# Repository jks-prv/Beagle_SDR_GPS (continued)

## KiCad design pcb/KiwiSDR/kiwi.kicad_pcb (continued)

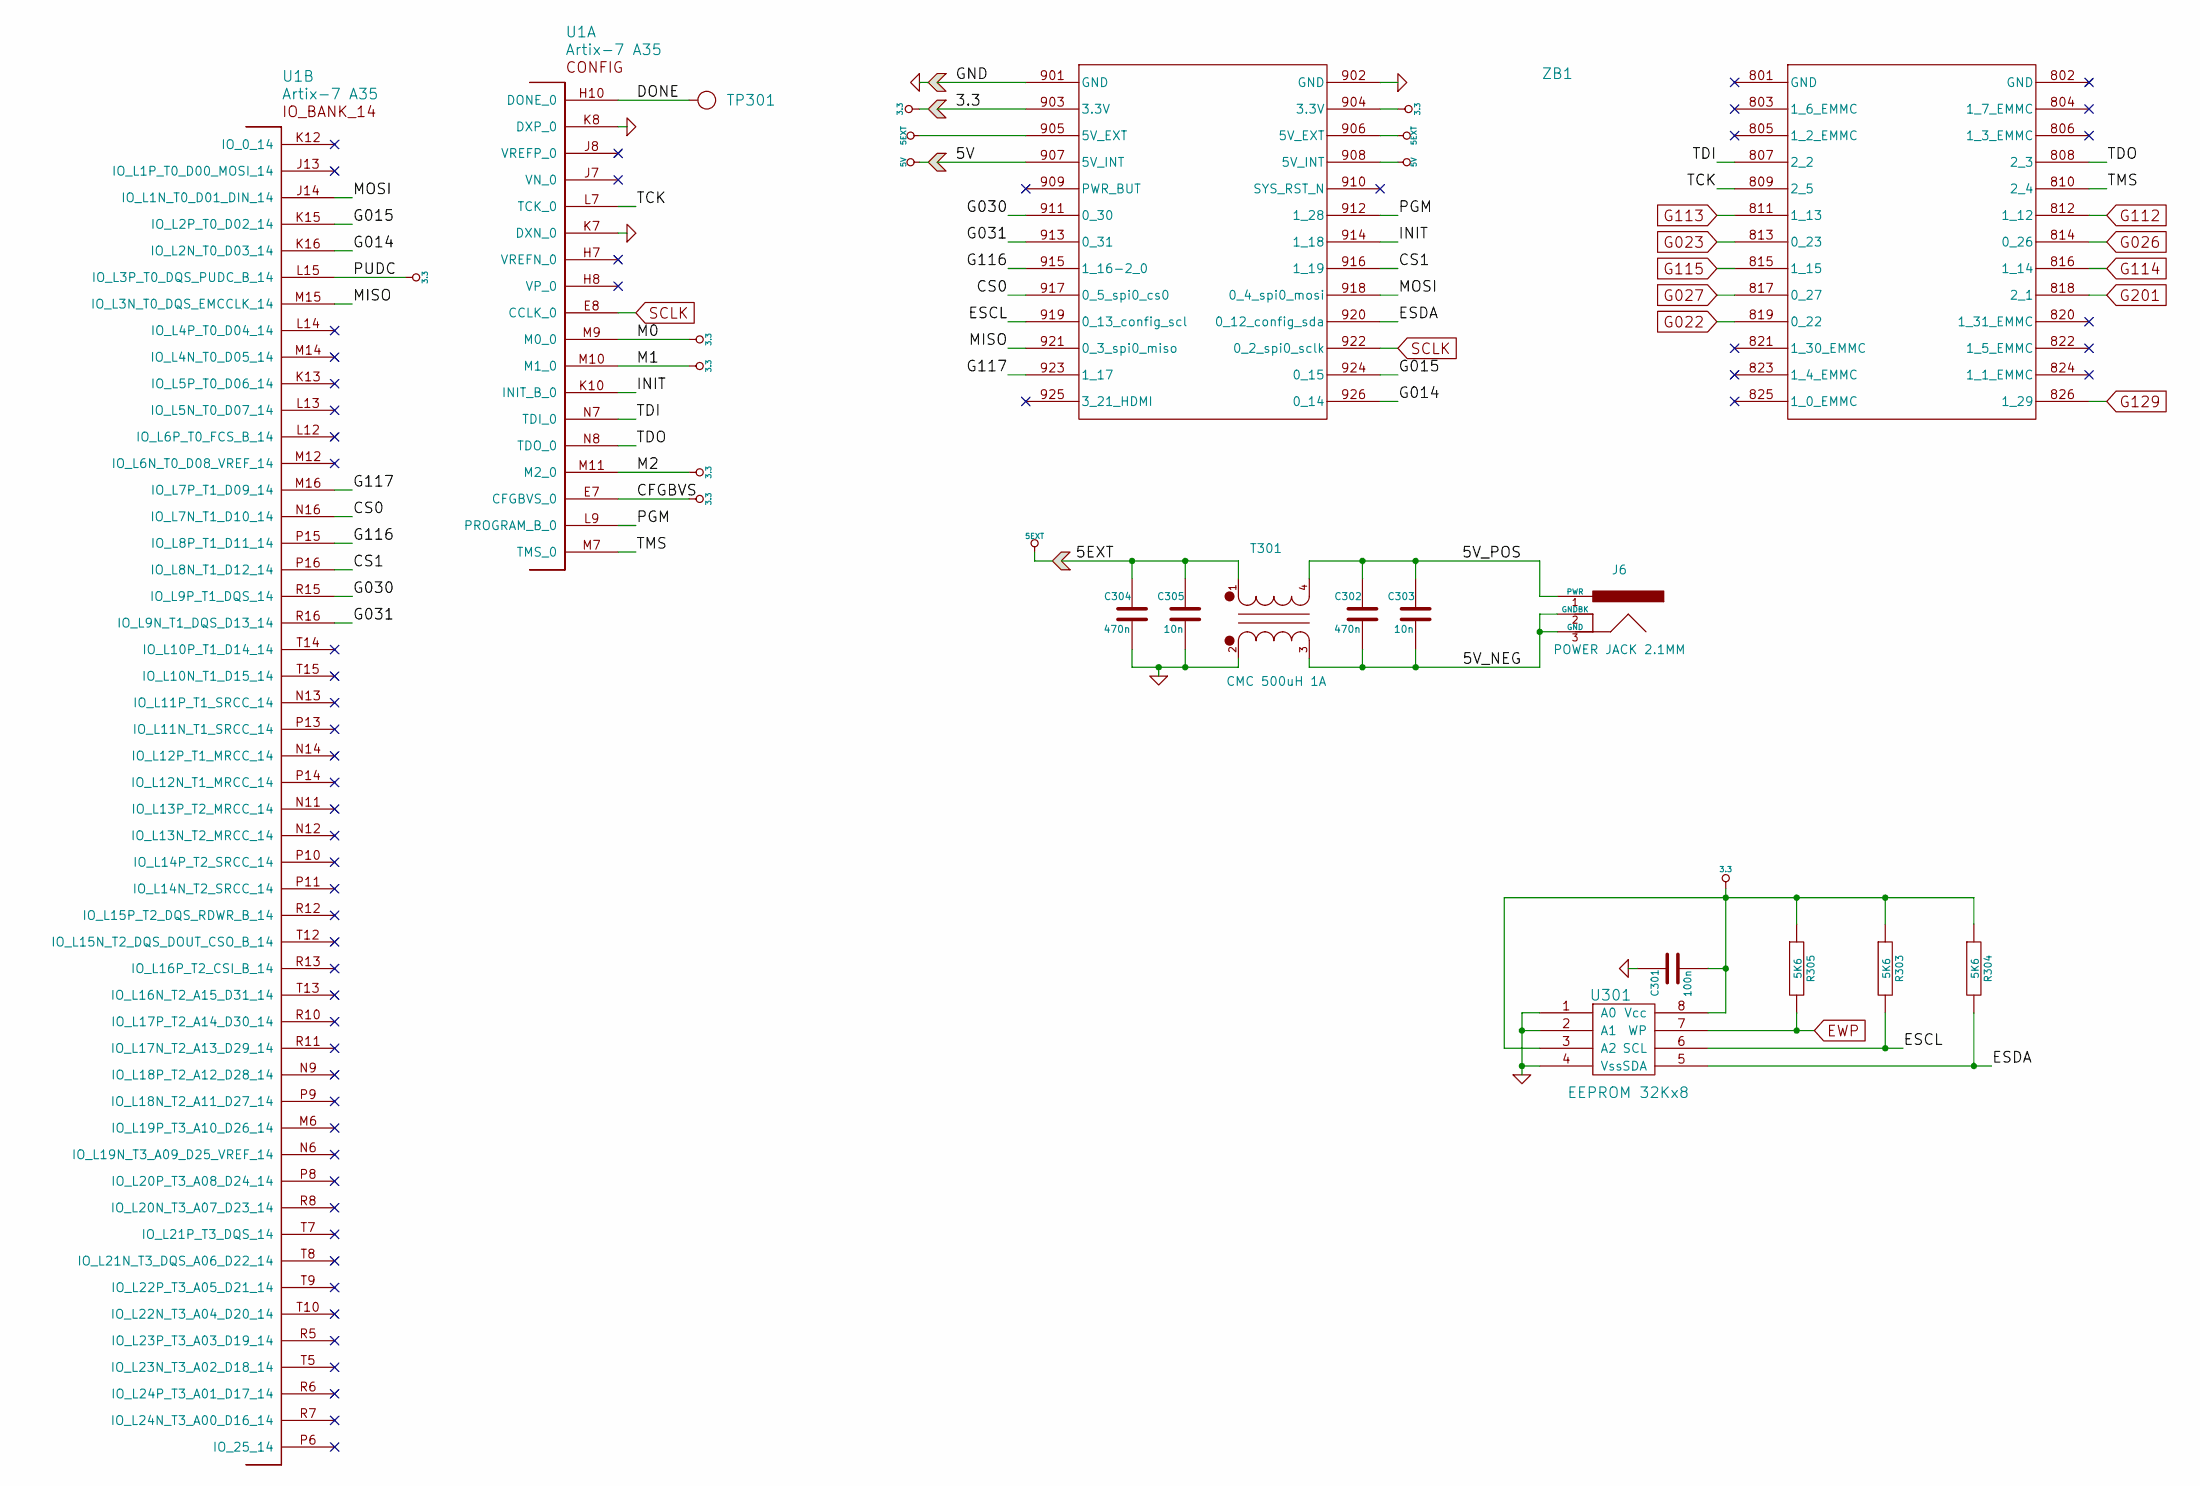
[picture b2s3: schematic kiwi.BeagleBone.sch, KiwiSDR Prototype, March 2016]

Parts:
C301: 100n; kiwi-SM0402
C302, C304: 470n; kiwi-SM0402
C303, C305: 10n; kiwi-SM0402
J6: POWER JACK 2.1MM; kiwi-JACK_2_1MM_TH
R303, R304, R305: 5K6; kiwi-SM0402
T301: CMC 500uH 1A; kiwi-CMC
TP301: TEST_POINT; kiwi-TP_VIA_600
U1: Artix-7 A35; kiwi-FTG256
U301: EEPROM 32Kx8; kiwi-TSSOP8
ZB1: HEADER 13x2; kiwi-BEAGLEBONE_BLACK

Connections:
/BeagleBone/5V_NEG: C302.2, C303.2, J6.2 (GNDBK), J6.3 (GND), T301.3
/BeagleBone/5V_POS: C302.1, C303.1, J6.1 (PWR), T301.4
/BeagleBone/CS0: U1.N16 (IO_L7N_T1_D10_14), ZB1.917 (0_5_spi0_cs0)
/BeagleBone/CS1: U1.P16 (IO_L8N_T1_D12_14), ZB1.916 (1_19)
/BeagleBone/DONE: TP301.1, U1.H10 (DONE_0)
/BeagleBone/ESCL: R303.2, U301.6 (SCL), ZB1.919 (0_13_config_scl)
/BeagleBone/ESDA: R304.2, U301.5 (SDA), ZB1.920 (0_12_config_sda)
/BeagleBone/G014: U1.K16 (IO_L2N_T0_D03_14), ZB1.926 (0_14)
/BeagleBone/G015: U1.K15 (IO_L2P_T0_D02_14), ZB1.924 (0_15)
/BeagleBone/G030: U1.R15 (IO_L9P_T1_DQS_14), ZB1.911 (0_30)
/BeagleBone/G031: U1.R16 (IO_L9N_T1_DQS_D13_14), ZB1.913 (0_31)
/BeagleBone/G116: U1.P15 (IO_L8P_T1_D11_14), ZB1.915 (1_16-2_0)
/BeagleBone/G117: U1.M16 (IO_L7P_T1_D09_14), ZB1.923 (1_17)
/BeagleBone/INIT: U1.K10 (INIT_B_0), ZB1.914 (1_18)
/BeagleBone/MISO: U1.M15 (IO_L3N_T0_DQS_EMCCLK_14), ZB1.921 (0_3_spi0_miso)
/BeagleBone/MOSI: U1.J14 (IO_L1N_T0_D01_DIN_14), ZB1.918 (0_4_spi0_mosi)
/BeagleBone/PGM: U1.L9 (PROGRAM_B_0), ZB1.912 (1_28)
/BeagleBone/TCK: U1.L7 (TCK_0), ZB1.809 (2_5)
/BeagleBone/TDI: U1.N7 (TDI_0), ZB1.807 (2_2)
/BeagleBone/TDO: U1.N8 (TDO_0), ZB1.808 (2_3)
/BeagleBone/TMS: U1.M7 (TMS_0), ZB1.810 (2_4)
EWP: R305.2, U301.7 (WP); also elsewhere on the board
G022: ZB1.819 (0_22); also elsewhere on the board
G023: ZB1.813 (0_23); also elsewhere on the board
G026: ZB1.814 (0_26); also elsewhere on the board
G027: ZB1.817 (0_27); also elsewhere on the board
G112: ZB1.812 (1_12); also elsewhere on the board
G113: ZB1.811 (1_13); also elsewhere on the board
G114: ZB1.816 (1_14); also elsewhere on the board
G115: ZB1.815 (1_15); also elsewhere on the board
G129: ZB1.826 (1_29); also elsewhere on the board
G201: ZB1.818 (2_1); also elsewhere on the board
SCLK: U1.E8 (CCLK_0), ZB1.922 (0_2_spi0_sclk); also elsewhere on the board

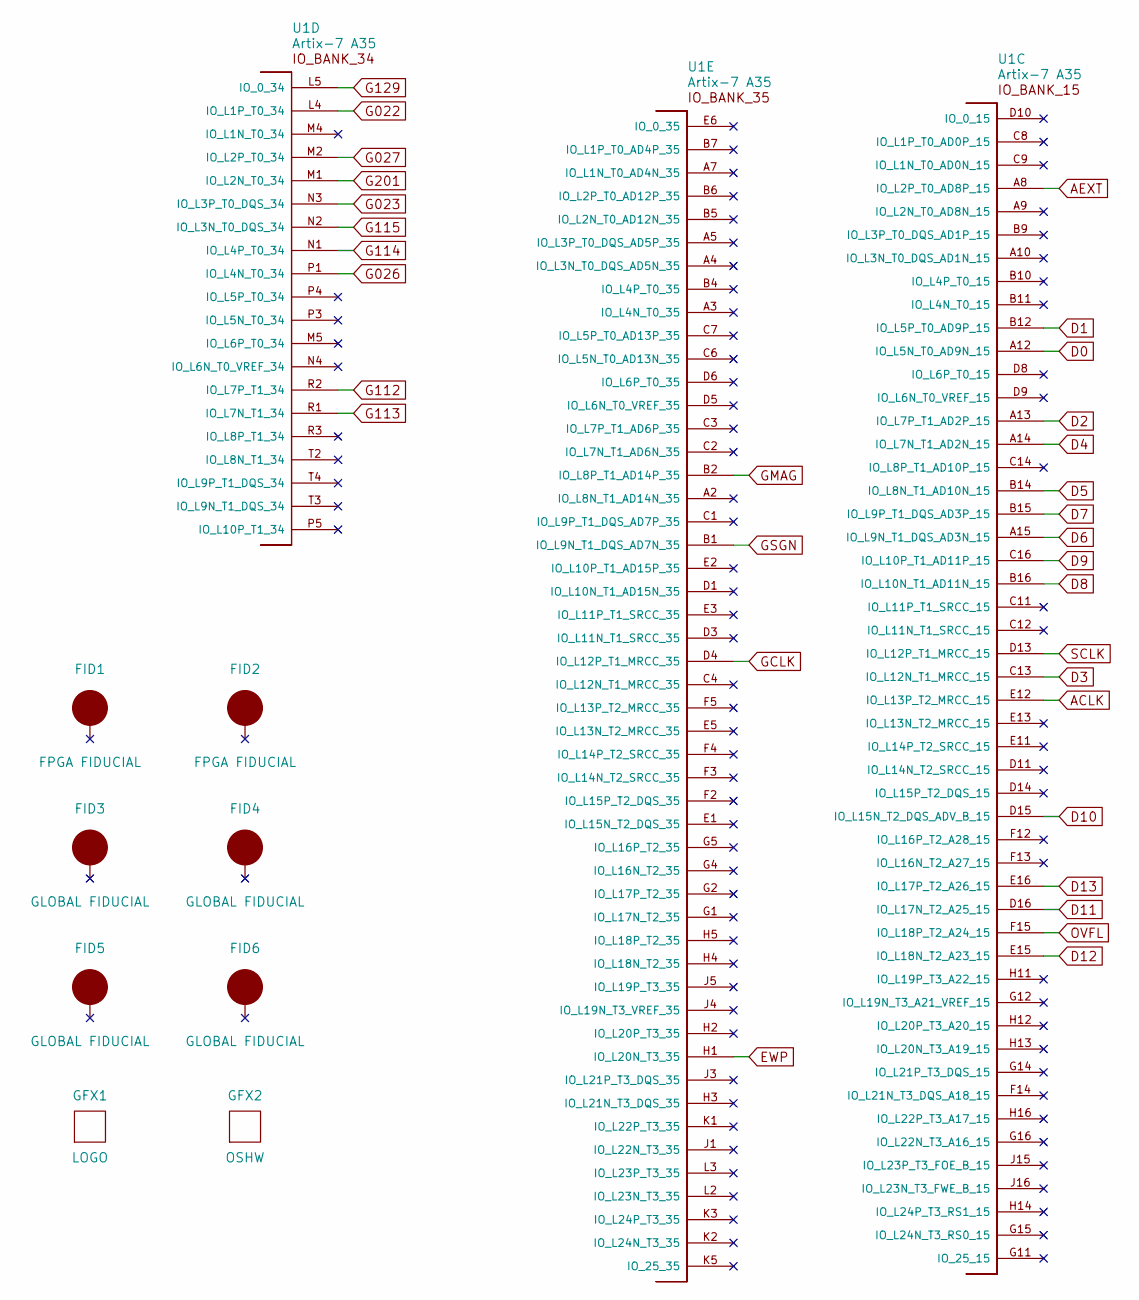
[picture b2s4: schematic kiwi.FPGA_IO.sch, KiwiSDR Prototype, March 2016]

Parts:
FID1, FID2: FPGA FIDUCIAL; kiwi-FIDUCIAL
FID3, FID4, FID5, FID6: GLOBAL FIDUCIAL; kiwi-FIDUCIAL
GFX1: LOGO; kiwi-KIWI_10MM
GFX2: OSHW; kiwi-OSHW_6MM
U1: Artix-7 A35; kiwi-FTG256

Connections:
ACLK: U1.E12 (IO_L13P_T2_MRCC_15); also elsewhere on the board
AEXT: U1.A8 (IO_L2P_T0_AD8P_15); also elsewhere on the board
D0: U1.A12 (IO_L5N_T0_AD9N_15); also elsewhere on the board
D1: U1.B12 (IO_L5P_T0_AD9P_15); also elsewhere on the board
D2: U1.A13 (IO_L7P_T1_AD2P_15); also elsewhere on the board
D3: U1.C13 (IO_L12N_T1_MRCC_15); also elsewhere on the board
D4: U1.A14 (IO_L7N_T1_AD2N_15); also elsewhere on the board
D5: U1.B14 (IO_L8N_T1_AD10N_15); also elsewhere on the board
D6: U1.A15 (IO_L9N_T1_DQS_AD3N_15); also elsewhere on the board
D7: U1.B15 (IO_L9P_T1_DQS_AD3P_15); also elsewhere on the board
D8: U1.B16 (IO_L10N_T1_AD11N_15); also elsewhere on the board
D9: U1.C16 (IO_L10P_T1_AD11P_15); also elsewhere on the board
D10: U1.D15 (IO_L15N_T2_DQS_ADV_B_15); also elsewhere on the board
D11: U1.D16 (IO_L17N_T2_A25_15); also elsewhere on the board
D12: U1.E15 (IO_L18N_T2_A23_15); also elsewhere on the board
D13: U1.E16 (IO_L17P_T2_A26_15); also elsewhere on the board
EWP: U1.H1 (IO_L20N_T3_35); also elsewhere on the board
G022: U1.L4 (IO_L1P_T0_34); also elsewhere on the board
G023: U1.N3 (IO_L3P_T0_DQS_34); also elsewhere on the board
G026: U1.P1 (IO_L4N_T0_34); also elsewhere on the board
G027: U1.M2 (IO_L2P_T0_34); also elsewhere on the board
G112: U1.R2 (IO_L7P_T1_34); also elsewhere on the board
G113: U1.R1 (IO_L7N_T1_34); also elsewhere on the board
G114: U1.N1 (IO_L4P_T0_34); also elsewhere on the board
G115: U1.N2 (IO_L3N_T0_DQS_34); also elsewhere on the board
G129: U1.L5 (IO_0_34); also elsewhere on the board
G201: U1.M1 (IO_L2N_T0_34); also elsewhere on the board
GCLK: U1.D4 (IO_L12P_T1_MRCC_35); also elsewhere on the board
GMAG: U1.B2 (IO_L8P_T1_AD14P_35); also elsewhere on the board
GSGN: U1.B1 (IO_L9N_T1_DQS_AD7N_35); also elsewhere on the board
OVFL: U1.F15 (IO_L18P_T2_A24_15); also elsewhere on the board
SCLK: U1.D13 (IO_L12P_T1_MRCC_15); also elsewhere on the board

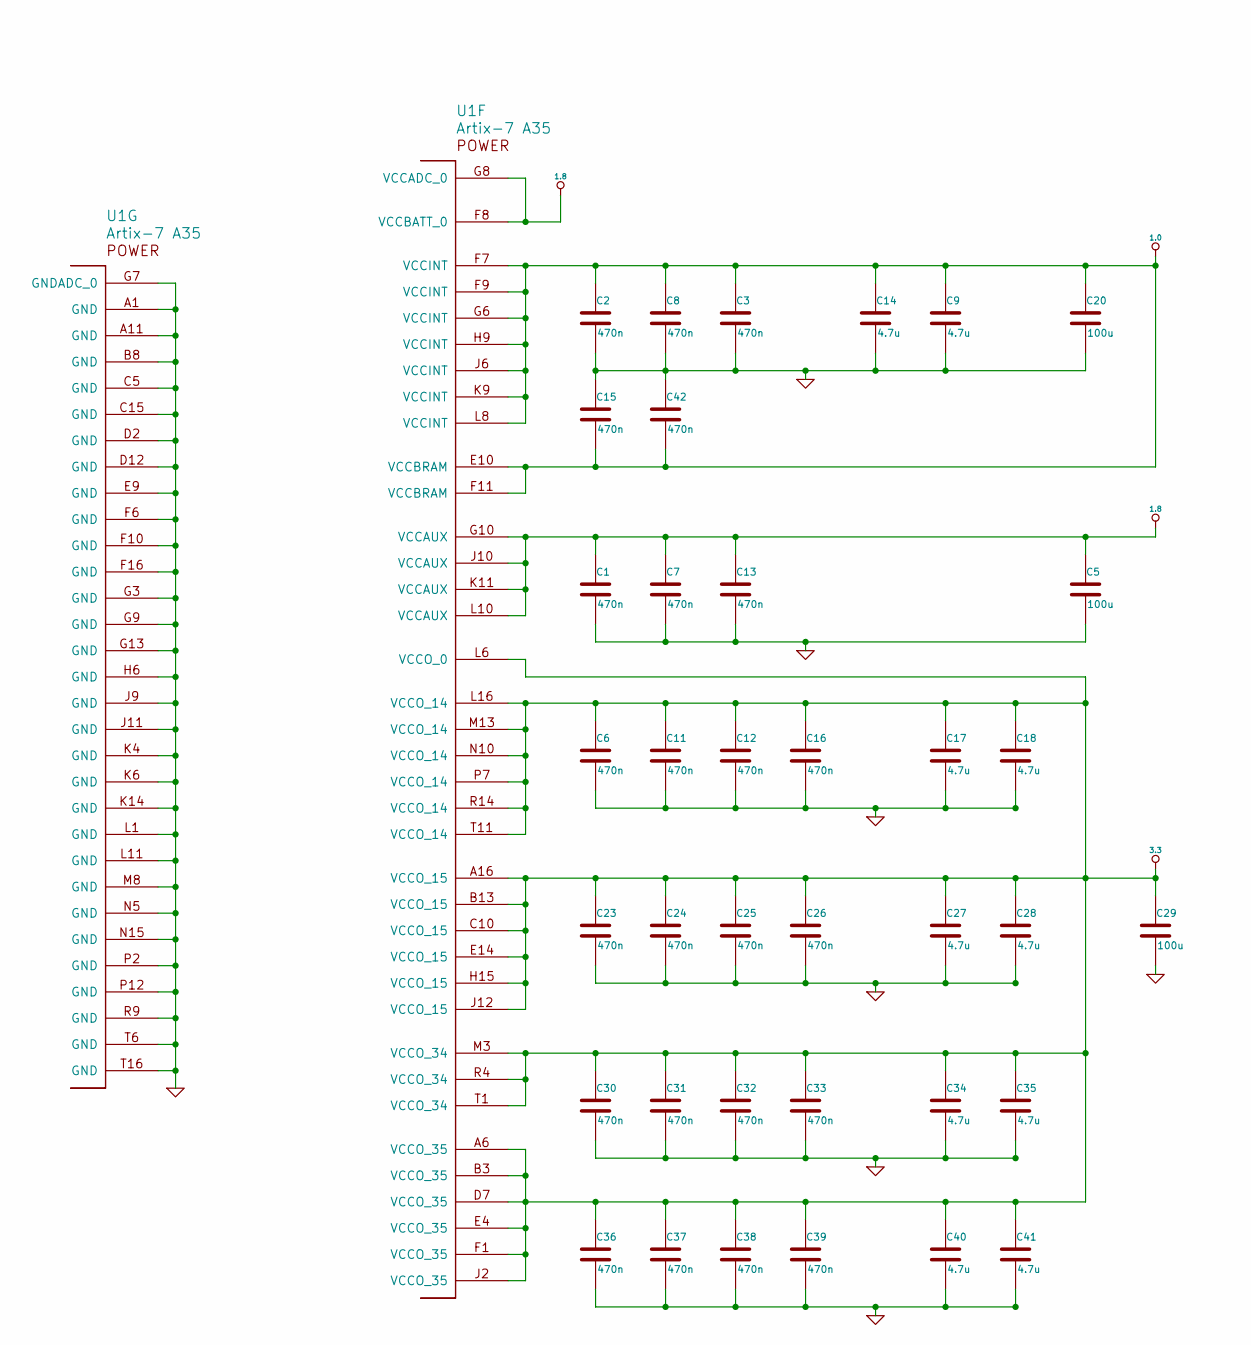
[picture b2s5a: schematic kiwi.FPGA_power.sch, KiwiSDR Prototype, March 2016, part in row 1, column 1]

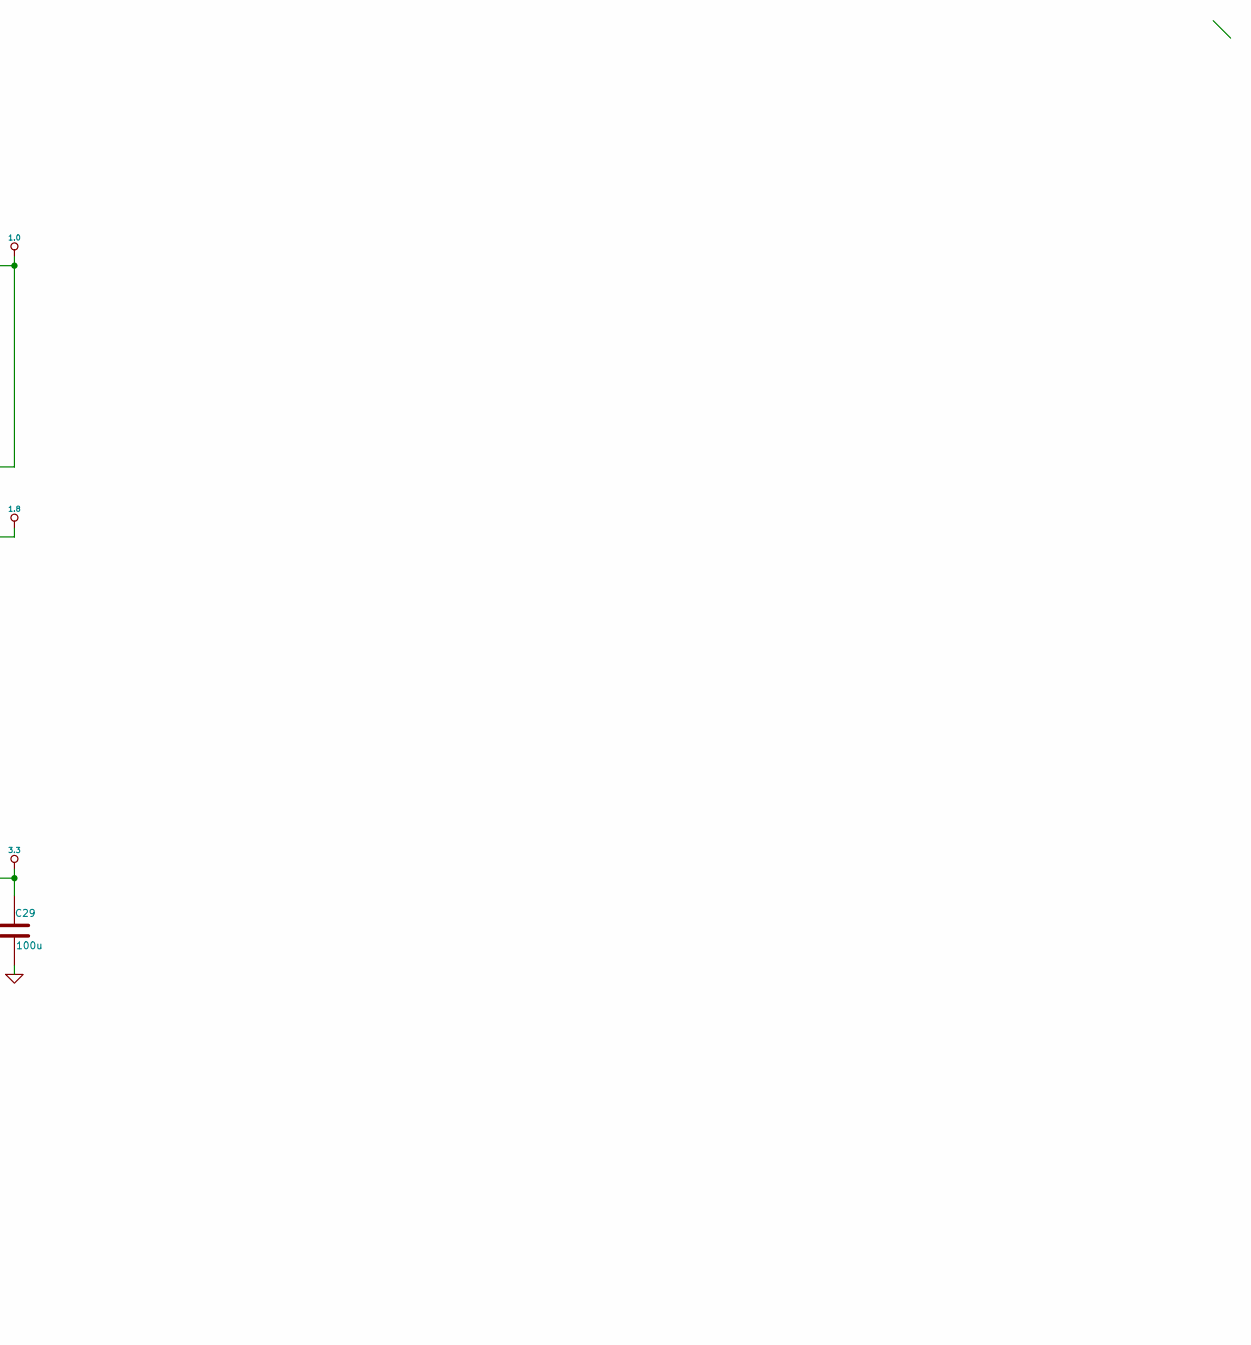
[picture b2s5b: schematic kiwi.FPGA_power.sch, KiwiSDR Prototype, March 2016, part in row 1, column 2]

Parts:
C1, C2, C3, C6, C7, C8, C11, C12, C13, C15, C16, C23, C24, C25, C26, C30, C31, C32, C33, C36, C37, C38, C39, C42: 470n; kiwi-SM0402
C5, C20, C29: 100u; kiwi-SM1206
C9, C14, C17, C18, C27, C28, C34, C35, C40, C41: 4.7u; kiwi-SM0402
U1: Artix-7 A35; kiwi-FTG256

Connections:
1.0: C2.1, C3.1, C8.1, C9.1, C14.1, C15.2, C20.1, C42.2, U1.E10 (VCCBRAM), U1.F7 (VCCINT), U1.F9 (VCCINT), U1.F11 (VCCBRAM), U1.G6 (VCCINT), U1.H9 (VCCINT), U1.J6 (VCCINT), U1.K9 (VCCINT), U1.L8 (VCCINT); also elsewhere on the board
1.8: C1.1, C5.1, C7.1, C13.1, U1.F8 (VCCBATT_0), U1.G8 (VCCADC_0), U1.G10 (VCCAUX), U1.J10 (VCCAUX), U1.K11 (VCCAUX), U1.L10 (VCCAUX); also elsewhere on the board

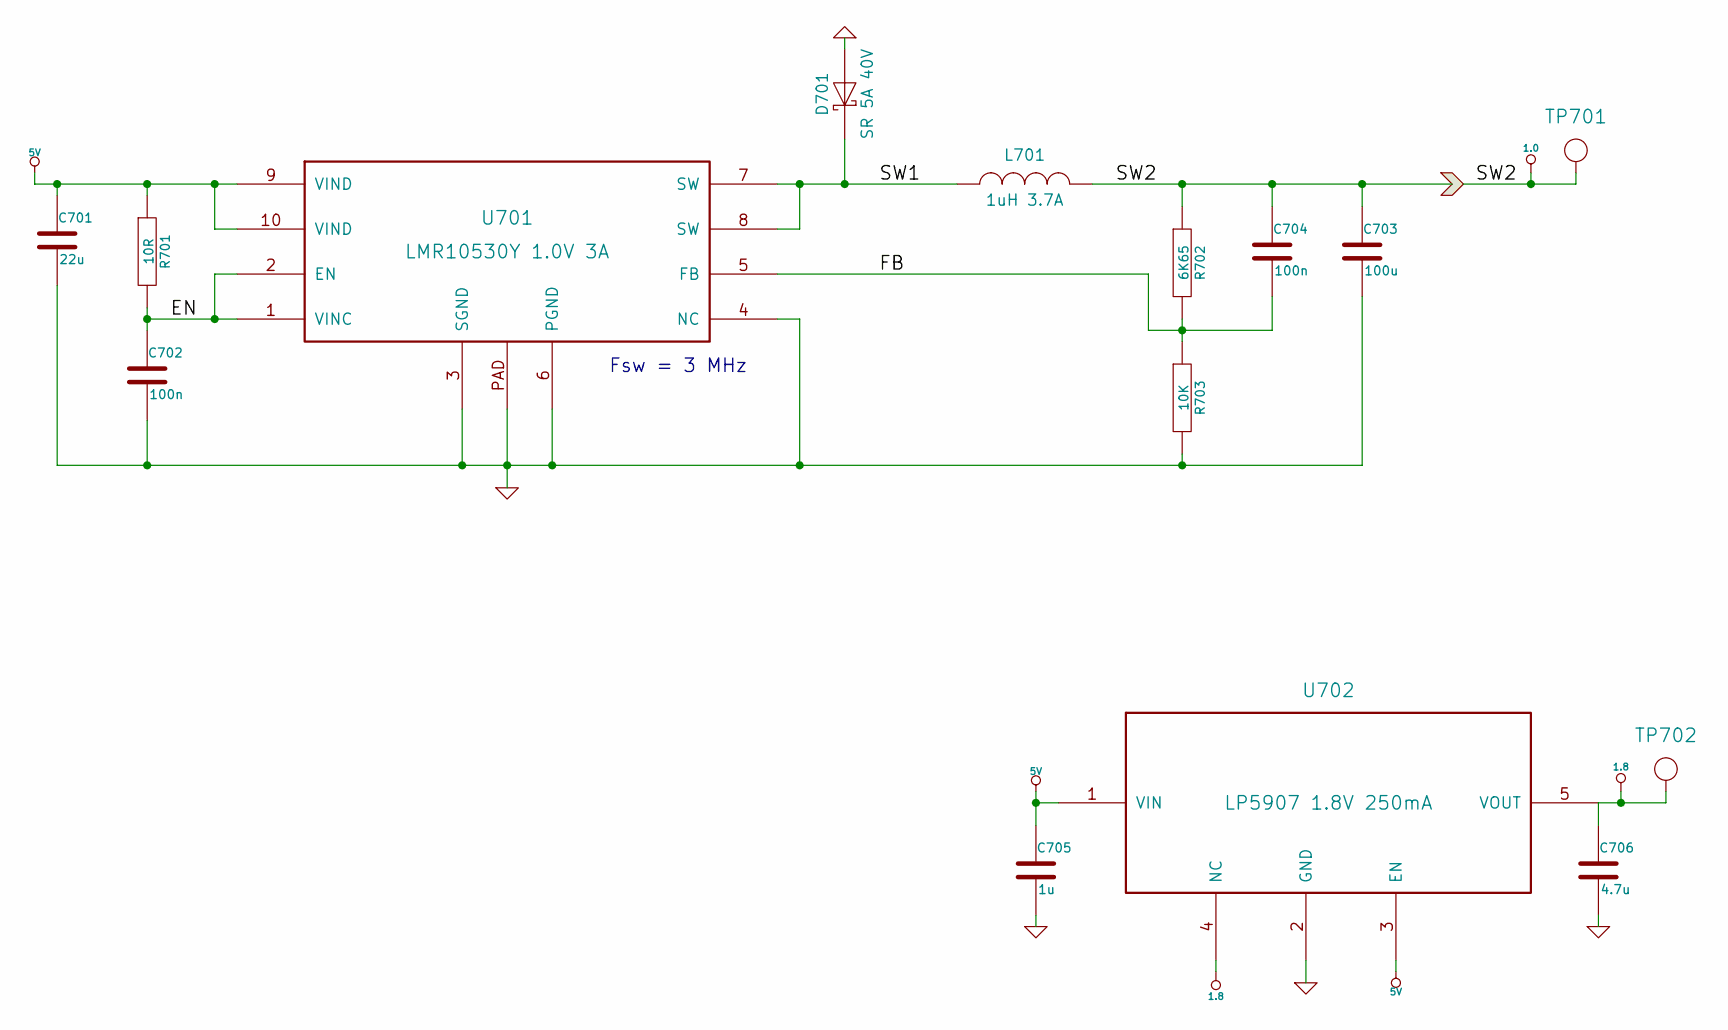
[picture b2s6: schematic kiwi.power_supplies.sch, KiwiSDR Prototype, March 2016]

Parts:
C701: 22u; kiwi-SM0805
C702, C704: 100n; kiwi-SM0402
C703: 100u; kiwi-SM1206
C705: 1u; kiwi-SM0402
C706: 4.7u; kiwi-SM0402
D701: SR 5A 40V; kiwi-DO214_AA
L701: 1uH 3.7A; kiwi-INDUCTOR_4x4
R701: 10R; kiwi-SM0402
R702: 6K65; kiwi-SM0402
R703: 10K; kiwi-SM0402
TP701, TP702: TEST_POINT; kiwi-TP_600
U701: LMR10530Y 1.0V 3A; kiwi-WSON10
U702: LP5907 1.8V 250mA; kiwi-SOT23_5

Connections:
1.0: C703.1, C704.1, L701.2, R702.1, TP701.1; also elsewhere on the board
1.8: C706.1, TP702.1, U702.4 (NC), U702.5 (VOUT); also elsewhere on the board
/Power_Supplies/EN: C702.1, R701.2, U701.1 (VINC), U701.2 (EN)
/Power_Supplies/FB: C704.2, R702.2, R703.1, U701.5 (FB)
/Power_Supplies/SW1: D701.1 (K), L701.1, U701.7 (SW), U701.8 (SW)

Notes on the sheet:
Fsw = 3 MHz

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
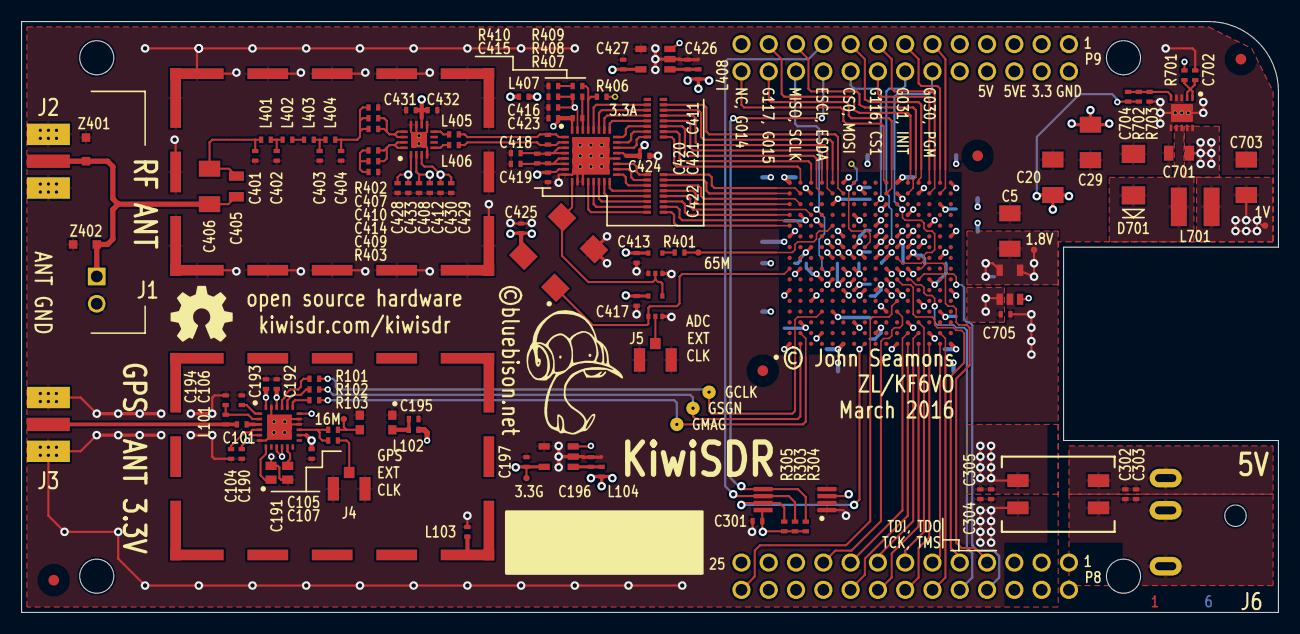
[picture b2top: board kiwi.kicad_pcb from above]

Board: 6 copper layers, 117.0 x 55.0 mm, 173 parts (0 on the bottom side), 119 nets.

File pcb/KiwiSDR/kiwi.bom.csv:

#1, 1, 0R, Panasonic, ERJ-2GE0R00X, kiwi-SM0402, R408
#2, 1, 10R, Panasonic, ERJ-2RKF10R0X, kiwi-SM0402, R701
#3, 1, 28R7, Panasonic, ERJ-2RKF28R7X, kiwi-SM0402, R403
#4, 1, 66R5, Panasonic, ERJ-2RKF66R5X, kiwi-SM0402, R402
#5, 4, 100R, Panasonic, ERJ-2RKF1000X, kiwi-SM0402, R101 R102 R103 R401
#6, 3, 5K6, Panasonic, ERJ-2RKF5601X, kiwi-SM0402, R303 R304 R305
#7, 1, 6K65, Panasonic, ERJ-2RKF6651X, kiwi-SM0402, R702
#8, 4, 10K, Panasonic, ERJ-2RKF1002X, kiwi-SM0402, R406 R409 R410 R703
#9, 2, 100R, Bourns, CAY16-101J8LF, kiwi-RNET_CAY16_J8, R404 R405
#10, 2, 22p, Murata, GRM1555C1H220JA01D, kiwi-SM0402, C101 C104
#11, 2, 56p/100, Murata, GRM1555C2A560JA01D, kiwi-SM0402, C401 C404
#12, 4, 100p, Murata, GRM1555C1H101JA01D, kiwi-SM0402, C194 C408 C411 C416
#13, 2, 160p/50, Murata, GRM1555C1H161JA01D, kiwi-SM0402, C402 C403
#14, 5, 1n, Murata, GCM155R71H102KA37D, kiwi-SM0402, C407 C409 C428 C430 C432
#15, 8, 10n, Murata, GRM155R71C103KA01D, kiwi-SM0402, C105 C106 C193 C303 C305 C413 C417 C425
#16, 14, 100n, Murata, GRM155R71C104KA88D, kiwi-SM0402, C190 C191 C192 C195 C301 C421 C422 C423 C424 C429 C431 C433 C702 C704
#17, 28, 470n, Murata, GRM155R6YA474KE01D, kiwi-SM0402, C1 C2 C3 C6 C7 C8 C11 C12 C13 C15 C16 C23 C24 C25 C26 C30 C31 C32 C33 C36 C37 C38 C39 C42 C302 C304 C410 C414
#18, 7, 1u, Murata, GRM155R61E105KA12D, kiwi-SM0402, C196 C197 C418 C419 C426 C427 C705
#19, 3, 2.2u, Murata, GRM155R60J225ME15D, kiwi-SM0402, C412 C415 C420
#20, 11, 4.7u, Murata, GRM155R60J475ME47D, kiwi-SM0402, C9 C14 C17 C18 C27 C28 C34 C35 C40 C41 C706
#21, 1, 1n/100, Murata, GRM219R72A102KA01J, kiwi-SM0805, C405
#22, 1, 22u, Murata, GRM21BR60J226ME39L, kiwi-SM0805, C701
#23, 1, 470n/100, AVX, ESD61C474K4T2A-28, kiwi-SM1206, C406
#24, 4, 100u, Murata, GRM31CR60J107ME39L, kiwi-SM1206, C5 C20 C29 C703
#25, 5, FB 600Z, TDK, MMZ1005B601C, kiwi-SM0402, L102 L103 L104 L407 L408
#26, 1, 39nH, TDK, MLK1005S39NJ, kiwi-SM0402, L101
#27, 3, 150nH, TDK, MLG1005SR15J, kiwi-SM0402, L403 L405 L406
#28, 1, 270nH, TDK, MLG1005SR27J, kiwi-SM0402, L402
#29, 2, 330nH, TDK, MLG1005SR33J, kiwi-SM0402, L401 L404
#30, 1, 1uH 3.7A, Bourns, SRN4018-1R0Y, kiwi-INDUCTOR_4x4, L701
#31, 1, CMC 500uH 1A, Bourns, SRF0905A-501Y, kiwi-CMC, T301
#32, 1, SAW L1, RFM, SF1186G, kiwi-SAW, FL101
#33, 1, SE4150L, Skyworks, SE4150L-R, kiwi-QFN24, U101
#34, 1, EEPROM 32Kx8, On Semi, CAT24C256YI-GT3, kiwi-TSSOP8, U301
#35, 2, NC7SZ125, Fairchild, NC7SZ125P5X, kiwi-SC70_5, U403 U406
#36, 1, LMR10530Y 1.0V 3A, TI, LMR10530YSD/NOPB, kiwi-WSON10, U701
#37, 2, LP5907 3.3V 250mA, TI, LP5907QMFX-3.3Q1, kiwi-SOT23_5, U104 U404
#38, 1, LP5907 1.8V 250mA, TI, LP5907QMFX-1.8Q1, kiwi-SOT23_5, U702
#39, 1, SR 5A 40V, Vishay, SSB44-E3/52T, kiwi-DO214_AA, D701
#40, 2, TVS 3.3V, Bourns, CDSOD323-T03C, kiwi-SOD323, Z401 Z402
#41, 1, 66.6666 MHz, Conner Winfield, CWX823-066.6666M, kiwi-XO, U402
#42, 1, 16.368 MHz, TXC, 7Q-16.368MBG-T, kiwi-TCXO, X101
#43, 2, RF_SHIELD 29x19, Laird, BMI-S-209-F, *, ZR401 ZR101
#44, 2, RF_SHIELD_COVER 29x19, Laird, BMI-S-209-C, kiwi-RF_SHIELD_COVER, ZR102 ZR402
#45, 1, Artix-7 A35, Xilinx, XC7A35T-1FTG256C, kiwi-FTG256, U1
#46, 1, LTC2248, Linear Tech, LTC2248CUH#PBF, kiwi-QFN32, U401
#47, 1, LTC6401-20, Linear Tech, LTC6401CUD-20#PBF, kiwi-QFN16, U405

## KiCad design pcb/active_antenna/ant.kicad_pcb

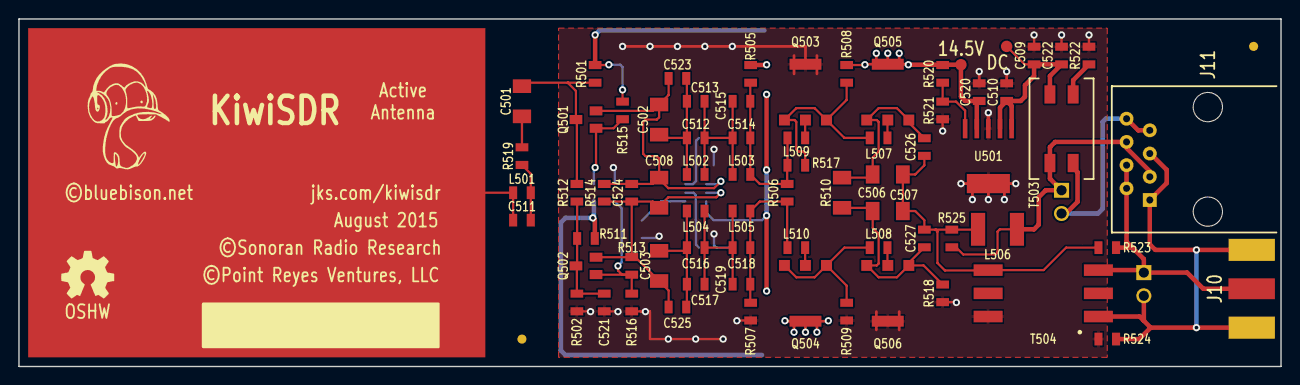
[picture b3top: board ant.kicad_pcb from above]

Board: 2 copper layers, 138.0 x 38.0 mm, 85 parts (0 on the bottom side), 36 nets.

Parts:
C501, C502, C503, C506, C507, C508: 470n/100; kiwi-SM1206
C504, C505: DNL 470n/100; kiwi-SM1206
C509: 100n/100; kiwi-SM0805
C510, C520: 10u/25; kiwi-SM0805
C511, C512, C513, C514, C515, C516, C517, C518, C519: DNL; kiwi-SM0805
C521: DNL 100n/100; kiwi-SM0805
C522, C523, C524, C525, C526, C527: 1n/100; kiwi-SM0805
EP501: E_FIELD_PROBE; kiwi-E_FIELD_PROBE
FID1, FID2: FIDUCIAL; kiwi-FIDUCIAL_2_SIDE
GFX1: LOGO; kiwi-KIWI_10MM
GFX3: OSHW; kiwi-OSHW_6MM
J10: DNL BNC; kiwi-BNC_SMA_NO_VIP
J11: DNL RJ45; kiwi-RJ45_8
J12: DNL TB_2; kiwi-TB_2P_2_54MM
J13: TB_2; kiwi-TB_2P_2_54MM
L501, L502, L503, L504, L505: 0R; kiwi-SM0805
L506: 100uH; kiwi-SM1812
L507, L508, L509, L510: FB 80Z; kiwi-SM0805
Q501: J310; kiwi-SOT23_DGS
Q502: J271; kiwi-SOT23_DGS
Q503, Q506: BFG31; kiwi-SOT223_EBEC
Q504, Q505: BFG35; kiwi-SOT223_EBEC
Q507: DNL J310; kiwi-SOT23_DGS
R501, R502: 1M; kiwi-SM0805
R503, R504: DNL 100R; kiwi-SM0805
R505, R507: 100K; kiwi-SM0805
R506: 2K2; kiwi-SM0805
R508, R509: 470R; kiwi-SM0805
R510: 10R/0.66W; kiwi-SM1206
R511: DNL 1M; kiwi-SM0805
R512, R515, R516, R519, R523, R524: 0R; kiwi-SM0805
R513, R518: DNL 0R; kiwi-SM0805
R514: 100R; kiwi-SM0805
R517: DNL 47R; kiwi-SM0805
R520: 11K; kiwi-SM0805
R521: 1K; kiwi-SM0805
R522: DNL; kiwi-SM0805
R525: 1K5; kiwi-SM0805
T501: DNL T-622; kiwi-MCL_KK81
T502, T504: DNL T1-6; kiwi-MCL_KK81
T503: CMC 2 mH; kiwi-CMC
TP501, TP502: TEST_POINT; kiwi-TP_1250
U501: TPS7A4501; kiwi-SOT223_6

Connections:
/14.55: C520.1, Q504.C, Q505.C, R501.1, R503.1, R505.1, R508.1, R511.1, R515.1, R520.1, T501.3, T502.4, TP502.1, U501.4
/ANT2: C511.2, L501.1, R519.1
/ANT3: C501.1, R519.2
/ANT4: C501.2, Q501.G, R501.2, R512.1
/B1H: L509.2, Q503.B
/B1L: L510.2, Q504.B
/B2H: L507.2, Q505.B
/B2L: L508.2, Q506.B
/BIAS: C521.1, Q502.G, R502.2, R511.2, R512.2
/BIAS+: J11.3, J11.6, J12.1, L506.2, R525.1, T503.3
/BIAS-: J11.7, J11.8, J12.2, T503.4
/DCIN: C509.1, C510.1, C522.1, T503.2, TP501.1, U501.1, U501.2
/E1H: L507.1, Q503.E1, Q503.E2, R508.2, R517.1
/E1L: L508.1, Q504.E1, Q504.E2, R509.1
/E2H: C506.1, C526.1, Q505.E1, Q505.E2, R510.1
/E2L: C507.1, C527.1, Q506.E1, Q506.E2, R510.2, R518.1
/EPROBE: C511.1, EP501.1, L501.2
/FB1: Q501.D, R515.2, T502.6
/FB2: Q502.D, Q507.G, R513.1, R516.2, T502.3
/FB3: Q507.D, T501.4
/JHI: C502.1, C508.1, C523.1, C524.1, Q501.S, R514.2, T501.1
/JLO: C503.1, C508.2, C524.2, C525.1, Q502.S, R513.2, R514.1, T501.2
/NF1H: C502.2, C512.1, C513.1, C523.2, L502.1
/NF1L: C503.2, C516.1, C517.1, C525.2, L504.1
/NF2H: C512.2, C513.2, C514.1, C515.1, L502.2, L503.1
/NF2L: C516.2, C517.2, C518.1, C519.1, L504.2, L505.1
/NF3H: C514.2, C515.2, L503.2, L509.1, R505.2, R506.1, R517.2
/NF3L: C518.2, C519.2, L505.2, L510.1, R506.2, R507.1
/OUT: C506.2, C507.2, C526.2, C527.2, L506.1, R523.2, R525.2, T504.3
/RX+: J10.1, J11.2, J11.4, J13.1, R523.1, T504.4
/RX-: J10.2, J10.3, J11.1, J11.5, J13.2, R524.1, T504.6
/THI: C505.1, R504.2, T501.6
/TLO: C504.2, R503.2, T501.5
/TP: R522.1, T503.1
/VADJ: R520.2, R521.2, U501.5
GND: C504.1, C505.2, C509.2, C510.2, C520.2, C521.2, C522.2, Q503.C, Q506.C, Q507.S, R502.1, R504.1, R507.2, R509.2, R516.1, R518.2, R521.1, R522.2, R524.2, T502.1, T504.1, U501.3, U501.TAB

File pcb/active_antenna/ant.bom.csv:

#1, 11, 0R, Panasonic, ERJ-6GEY0R00V, kiwi-SM0805, L501 L502 L503 L504 L505 R512 R515 R516 R519 R523 R524
#2, 1, 100R, Panasonic, ERJ-6ENF1000V, kiwi-SM0805, R514
#3, 2, 470R, Panasonic, ERJ-6ENF4700V, kiwi-SM0805, R508 R509
#4, 1, 1K, Panasonic, ERJ-6ENF1001V, kiwi-SM0805, R521
#5, 1, 1K5, Panasonic, ERJ-6ENF1501V, kiwi-SM0805, R525
#6, 1, 2K2, Panasonic, ERJ-6ENF2201V, kiwi-SM0805, R506
#7, 1, 11K, Panasonic, ERJ-6ENF1102V, kiwi-SM0805, R520
#8, 2, 100K, Panasonic, ERJ-6ENF1003V, kiwi-SM0805, R505 R507
#9, 2, 1M, Panasonic, ERJ-6ENF1004V, kiwi-SM0805, R501 R502
#10, 1, 10R/0.66W, Panasonic, ERJ-P08F10R0V, kiwi-SM1206, R510
#11, 6, 1n/100, Murata, GRM219R72A102KA01J, kiwi-SM0805, C522 C523 C524 C525 C526 C527
#12, 1, 100n/100, Murata, GRM21BR72A103KA01L, kiwi-SM0805, C509
#13, 2, 10u/25, Murata, GRM219R61E106KA12D, kiwi-SM0805, C510 C520
#14, 6, 470n/100, AVX, ESD61C474K4T2A-28, kiwi-SM1206, C501 C502 C503 C506 C507 C508
#15, 1, 100uH, TDK, B82432T1104K, kiwi-SM1812, L506
#16, 1, CMC 2 mH, Bourns, SRF0905A-202Y, kiwi-CMC, T503
#17, 1, J310, Fairchild, MMBFJ310, kiwi-SOT23_DGS, Q501
#18, 2, BFG35, NXP, BFG35.115, kiwi-SOT223_EBEC, Q504 Q505
#19, 1, TPS7A4501, TI, TPS7A4501DCQR, kiwi-SOT232_6, U501
#20, 4, FB 80Z, TDK, MMZ2012D800B, kiwi-SM0805, L507 L508 L509 L510
#21, 1, TB_2, TE Conn, 282834-2, kiwi-TB_2P_2_54MM, J13
#22, 1, J271, Fairchild, MMBFJ271, kiwi-SOT23_DGS, Q502
#23, 2, BFG31, NXP, BFG31.115, kiwi-SOT223_EBEC, Q503 Q506
